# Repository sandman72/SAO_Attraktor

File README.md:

# SAO_Attraktor
Attraktor Logo as a SAO (Shitty / Supercon Add On)

Runs pixel animations on the Attraktor SAO Badge's 42 (! of course) LEDs

KiCAD 8.0 Project with Schematics, PCB, Gerbers and Testcode 
for the Attraktor SAO PCB we show at the Hackaday Conference 2025.

Runs pixel animations on the Attraktor SAO Badge's 42 (! of course) LEDs

The Arduino code works with the following CH32V003 MCUs from the board manager:
  - CH32 MCU EVT Boards 1.0.4 or later (WCHLinkRV driver)
  - or WCH32 Boards 0.0.2 (WinUSB driver) 

Upload needs the CH32V003 WCH-LinkE dongle in RISC-V mode.

For the SAO Board to work correctly you need to reflash the MCU 
with the WCH-LinkUtility once to disable the NRST functionality on pin PD7:

  "Disable mul-func, PD7 is used for IO func"

Beware that the Eval Boards use pin PA1 and PA2 for external clock crystal 
and PD7 for Reset and therefore cannot be used for testing. Pin PD1 is 
used for programming via SWDIO

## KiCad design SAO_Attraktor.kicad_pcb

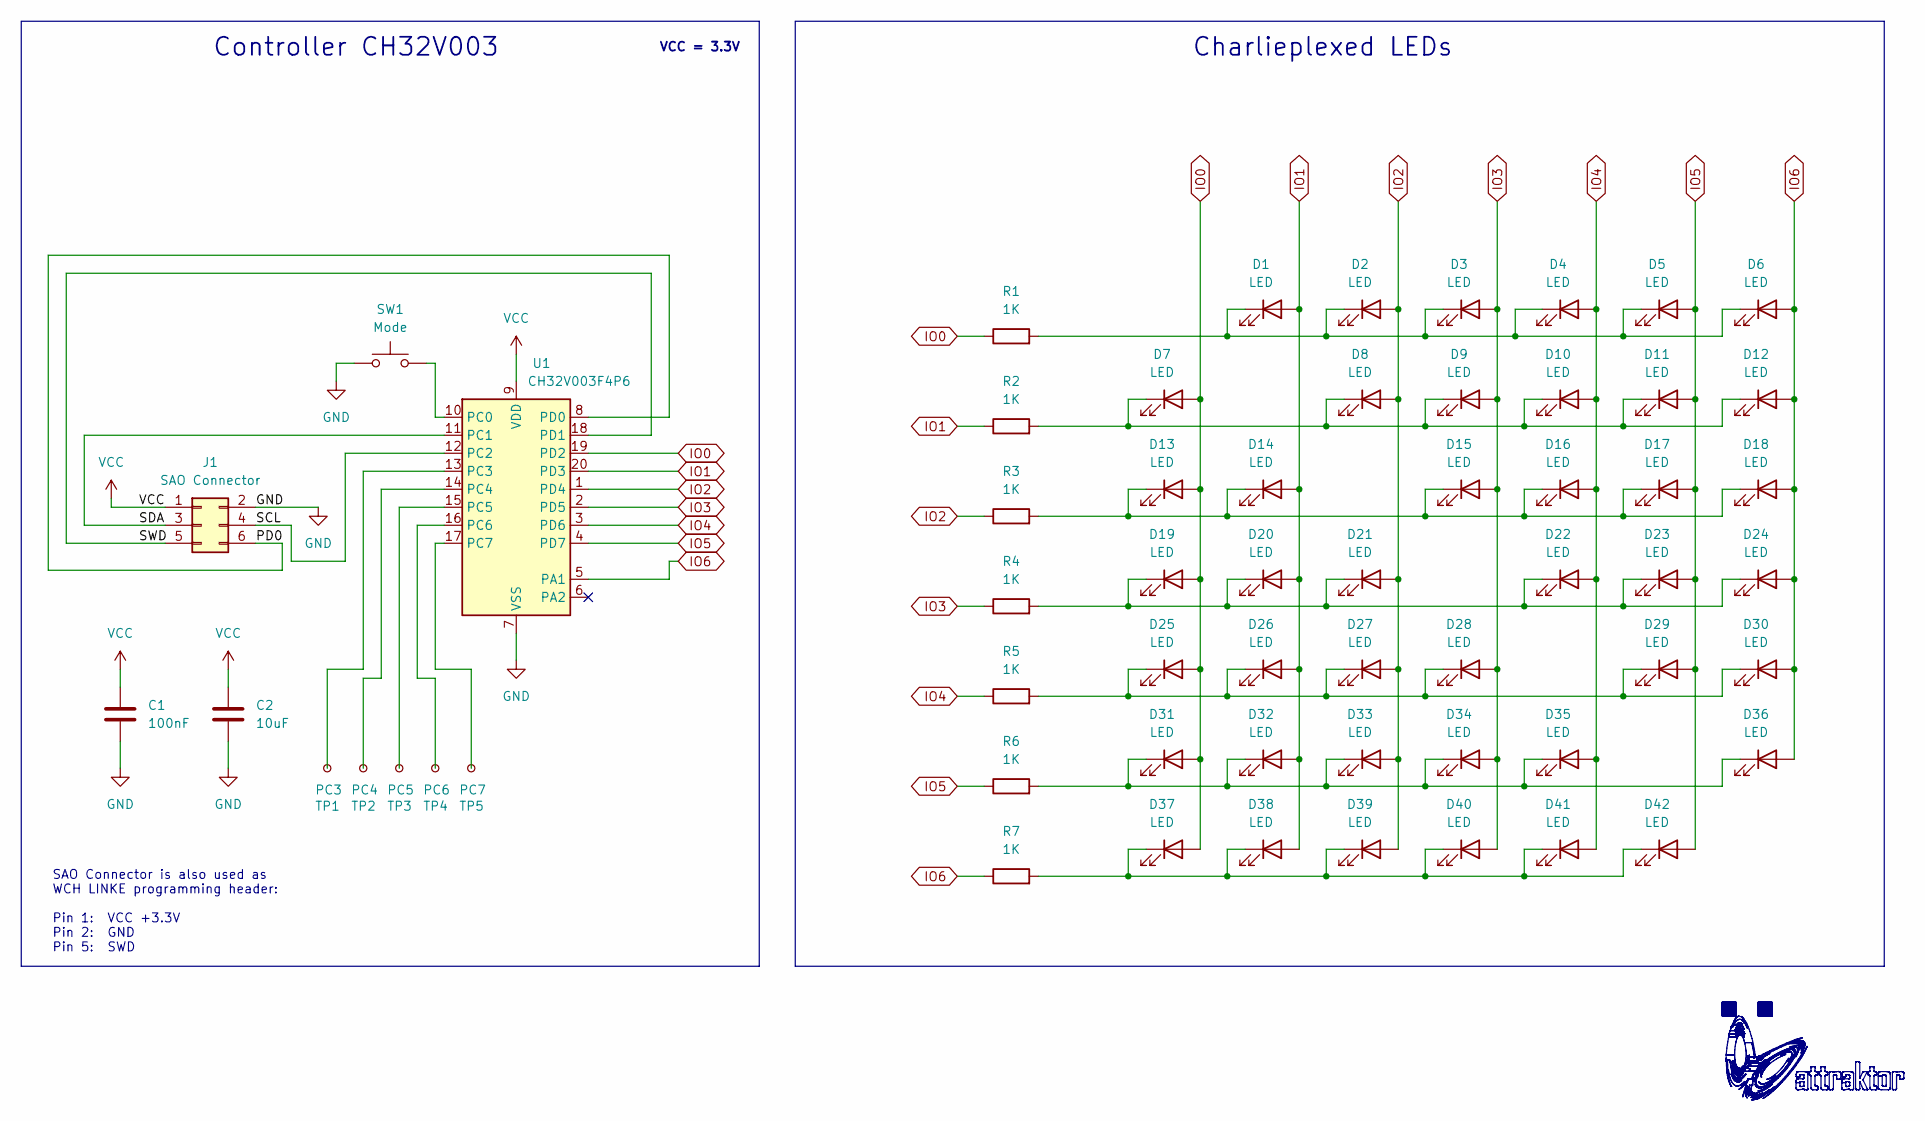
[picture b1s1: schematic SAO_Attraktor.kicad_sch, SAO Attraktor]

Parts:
C1: 100nF; C_0603_1608Metric
C2: 10uF; C_0603_1608Metric
D1, D2, D3, D4, D5, D6, D7, D8, D9, D10, D11, D12, D13, D14, D15, D16, D17, D18, D19, D20, D21, D22, D23, D24, D25, D26, D27, D28, D29, D30, D31, D32, D33, D34, D35, D36, D37, D38, D39, D40, D41, D42: LED; LED_0603_1608Metric
J1: SAO Connector; PinHeader_2x03_P2.54mm_Vertical_SMD
R1, R2, R3, R4, R5, R6, R7: 1K; R_0603_1608Metric
SW1: Mode; SW_SPST_PTS810
TP1: PC3; TestPoint_Pad_D1.5mm
TP2: PC4; TestPoint_Pad_D1.5mm
TP3: PC5; TestPoint_Pad_D1.5mm
TP4: PC6; TestPoint_Pad_D1.5mm
TP5: PC7; TestPoint_Pad_D1.5mm
U1: CH32V003F4P6; TSSOP-20_4.4x6.5mm_P0.65mm

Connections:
/PD0: J1.6, U1.8 (PD0)
/SCL: J1.4, U1.12 (PC2)
/SDA: J1.3, U1.11 (PC1)
/SWD: J1.5, U1.18 (PD1)
GND: C1.2, C2.2, J1.2, SW1.1, U1.7 (VSS)
IO0: D7.2 (A), D13.2 (A), D19.2 (A), D25.2 (A), D31.2 (A), D37.2 (A), R1.1, U1.19 (PD2)
IO1: D1.2 (A), D14.2 (A), D20.2 (A), D26.2 (A), D32.2 (A), D38.2 (A), R2.1, U1.20 (PD3)
IO2: D2.2 (A), D8.2 (A), D21.2 (A), D27.2 (A), D33.2 (A), D39.2 (A), R3.1, U1.1 (PD4)
IO3: D3.2 (A), D9.2 (A), D15.2 (A), D28.2 (A), D34.2 (A), D40.2 (A), R4.1, U1.2 (PD5)
IO4: D4.2 (A), D10.2 (A), D16.2 (A), D22.2 (A), D35.2 (A), D41.2 (A), R5.1, U1.3 (PD6)
IO5: D5.2 (A), D11.2 (A), D17.2 (A), D23.2 (A), D29.2 (A), D42.2 (A), R6.1, U1.4 (PD7)
IO6: D6.2 (A), D12.2 (A), D18.2 (A), D24.2 (A), D30.2 (A), D36.2 (A), R7.1, U1.5 (PA1)
unnamed: D1.1 (K), D2.1 (K), D3.1 (K), D4.1 (K), D5.1 (K), D6.1 (K), R1.2
unnamed: D7.1 (K), D8.1 (K), D9.1 (K), D10.1 (K), D11.1 (K), D12.1 (K), R2.2
unnamed: D13.1 (K), D14.1 (K), D15.1 (K), D16.1 (K), D17.1 (K), D18.1 (K), R3.2
unnamed: D19.1 (K), D20.1 (K), D21.1 (K), D22.1 (K), D23.1 (K), D24.1 (K), R4.2
unnamed: D25.1 (K), D26.1 (K), D27.1 (K), D28.1 (K), D29.1 (K), D30.1 (K), R5.2
unnamed: D31.1 (K), D32.1 (K), D33.1 (K), D34.1 (K), D35.1 (K), D36.1 (K), R6.2
unnamed: D37.1 (K), D38.1 (K), D39.1 (K), D40.1 (K), D41.1 (K), D42.1 (K), R7.2
unnamed: SW1.2, U1.10 (PC0)
unnamed 20: TP1.1, U1.13 (PC3); also elsewhere on the board
unnamed 21: TP2.1, U1.14 (PC4); also elsewhere on the board
unnamed 22: TP3.1, U1.15 (PC5); also elsewhere on the board
unnamed 23: TP4.1, U1.16 (PC6); also elsewhere on the board
unnamed 24: TP5.1, U1.17 (PC7); also elsewhere on the board
VCC: C1.1, C2.1, J1.1, U1.9 (VDD)

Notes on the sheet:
Charlieplexed LEDs
VCC = 3.3V
Controller CH32V003
SAO Connector is also used as WCH LINKE programming header: Pin 1: VCC +3.3V Pin 2: GND Pin 5: SWD

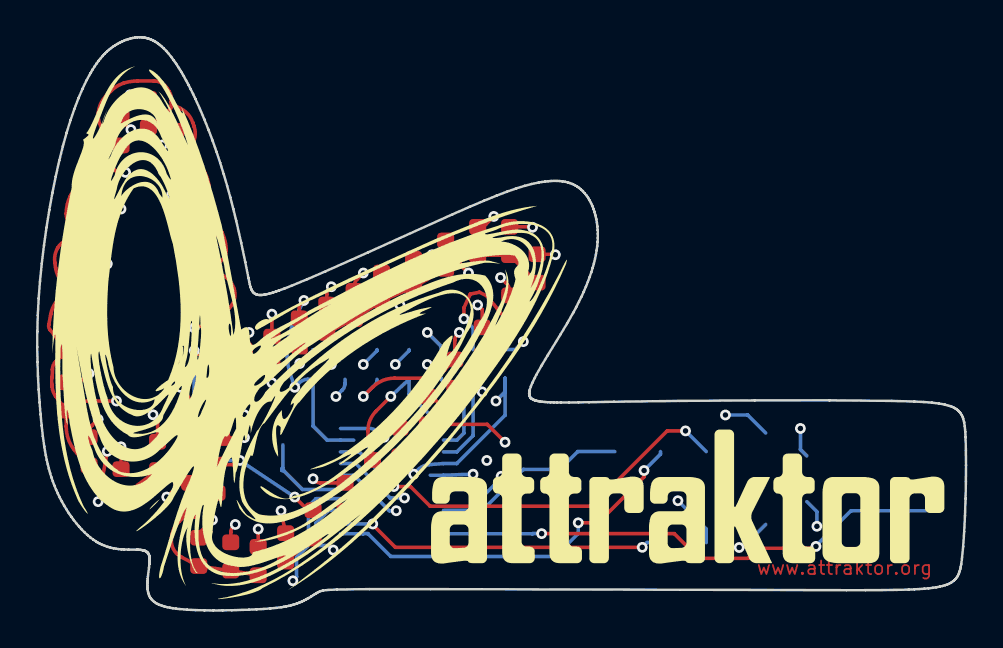
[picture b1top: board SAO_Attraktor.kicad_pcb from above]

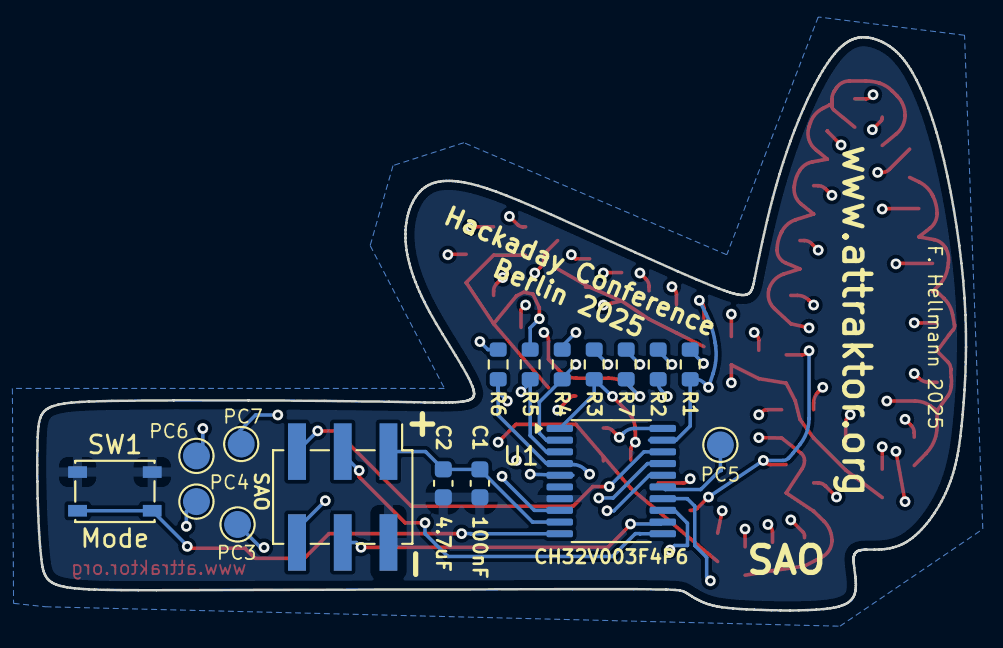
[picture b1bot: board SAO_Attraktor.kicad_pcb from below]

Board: 4 copper layers, 51.6 x 31.8 mm, 59 parts (17 on the bottom side), 26 nets.

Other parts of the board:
PC3: PC3; TestPoint_Pad_D1.5mm
PC4: PC4; TestPoint_Pad_D1.5mm
PC5: PC5; TestPoint_Pad_D1.5mm
PC6: PC6; TestPoint_Pad_D1.5mm
PC7: PC7; TestPoint_Pad_D1.5mm

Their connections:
unnamed 20: PC3.1; also elsewhere on the board
unnamed 21: PC4.1; also elsewhere on the board
unnamed 22: PC5.1; also elsewhere on the board
unnamed 23: PC6.1; also elsewhere on the board
unnamed 24: PC7.1; also elsewhere on the board

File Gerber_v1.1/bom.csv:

Designator,Footprint,Quantity,Value,LCSC Part #
C1,0603,1,100nF,
C2,0603,1,4.7uF,
"D1, D10, D11, D12, D13, D14, D15, D16, D17, D18, D19, D2, D20, D21, D22, D23, D24, D25, D26, D27, D28, D29, D3, D30, D31, D32, D33, D34, D35, D36, D37, D38, D39, D4, D40, D41, D42, D5, D6, D7, D8, D9",0603,42,LED,
J1,PinHeader_2x03_P2.54mm_Vertical_SMD,1,SAO,
PC3,TestPoint_Pad_D1.5mm,1,PC3,
PC4,TestPoint_Pad_D1.5mm,1,PC4,
PC5,TestPoint_Pad_D1.5mm,1,PC5,
PC6,TestPoint_Pad_D1.5mm,1,PC6,
PC7,TestPoint_Pad_D1.5mm,1,PC7,
"R1, R2, R3, R4, R5, R6, R7",0603,7,1K,
SW1,SW_SPST_PTS810,1,Mode,
U1,TSSOP-20_4.4x6.5mm_P0.65mm,1,CH32V003F4P6,

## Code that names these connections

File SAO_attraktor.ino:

/*
  Runs the pixel animation on the Attraktor SAO Badge

  modified 10 Jan 2025
  by Frank Hellmann

  This example code is in the public domain.

  Works with CH32 MCU EVT Boards 1.0.4 or later (WCHLinkRV driver) or WCH32 Boards 0.0.2 (WinUSB driver)

  For the SAO Board you need to reflash the MCU with the WCH-LinkUtility once to disable the NRST functionality on pin PD7:
  "Disable mul-func, PD7 is used for IO func"

  Beware that the Eval Boards use pin PA1 and PA2 for external clock crystal and PD7 for Reset and therefore cannot be used for testing

  Pin PD1 is used for programming via SWDIO

*/

int count = 0;
int mode = 1;

// our output pins for charlieplexing on SAO board
int led_pins[] = {PD2,PD3,PD4,PD5,PD6,PD7,PA1};
int button = PD0;

// clear digital pins
void clear_led() {
  for (int i=0; i<7; i++) { 
    pinMode(led_pins[i], INPUT); 
  }
}

void set_led(int led){
  led=1+led+led/7;
  int row = led/7;
  int col = led%7;
  pinMode(led_pins[row], OUTPUT);
  digitalWrite(led_pins[row], LOW); 
  pinMode(led_pins[col], OUTPUT);
  digitalWrite(led_pins[col], HIGH); 
 }

// the setup function runs once when you press reset or power the board
void setup() {
  // disable external clock and free up pin PA1
  AFIO->PCFR1 = AFIO->PCFR1 & 0xFFFF7FFF;
  // initialize digital pins as floating, eg. input.
  clear_led();
  // initialize button input for mode change
  pinMode(D0,INPUT);
}

// the loop function runs over and over again forever
void loop() {
  clear_led();
  set_led(count++);
  if (count>41) {
    count=0;
    if(mode>1){
      clear_led();
      delay(random(10000));
    }
  }
  if (mode>0) {
    if (count<22) { delayMicroseconds(1500 + count*500); }
    if (count>21) { delayMicroseconds(1500 + (42-count) * 500); }
    //delayMicroseconds(3500);
  }
}

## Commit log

2025-01-21 Initial commit of Version 1.1
    Version 1.1 adds extra breakout pads for I/O Pins PC3-PC7
2025-01-21 Arduino Demo Code and Documentation
2025-01-21 Images uploaded
2025-01-31 Added Position and BOM files
